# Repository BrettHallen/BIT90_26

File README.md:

# BIT90/26
An attempted recreation of the BIT90 computer released by Bit Corporation (普澤有限公司) in 1983 that is about [US$90,000 (AU$125,000) cheaper than a used one](https://web.archive.org/web/20260206154213/https://www.ebay.com/itm/127471879150):<br>
- Z80 CPU
- TMS9929A VDP
- 2KB RAM (one TC5517/4016 SRAM) expandable to 32KB (expansion cartridge)
- 16KB VRAM (eight 4116 DRAM)
- 24KB ROM (two 2364 + one 2764 or a variation) containing BASIC & Colecovision firmware (?)
- RF & composite video output
- two joystick ports
- Colecovision cartridge/tape compatible (2x15 pin)
- combination audio/video/tape port (DE9)
- expansion edge connector (2x30 pin)
- 5-pin DIN for power (±5V & +12V)

Heavily relying on all the excellent information shared by [b3rendsh](https://github.com/b3rendsh) in their [BIT90 repository](https://github.com/b3rendsh/bit90).<br>

## [Part 1](/KiCad/BIT90_Original/) - Completed (enough)
The initial aim of the project is to recreate the original schematics in KiCad:<br>
- Sheet 6-1 (Processor): ✅ completed
- Sheet 6-2 (Video Control): ✅ completed
- Sheet 6-3 (Joystick, Audio, Tape): ✅ completed
- Sheet 6-4 (Keyboard): ✅ completed
- Sheet 6-5 (PAL Video Encoder): ❌ lost interest, using a Pico9918 so no point
- Sheet 6-6 (Expansion): ✅ completed
- Sheet 7-5 (PAL Video Encoder/32K): ❌ not needed for recreation
- 32K DRAM (4416x4): 🤔 pending, if I can get the base model working

The Video Encoder schematic isn't really relevant to my proposed re-design so haven't bothered completing them.<br>

Sheet 7-5 and the 32KB DRAM sheets appear to be for an updated system with 32KB of RAM?  This would be the ultimate aim, but let's see if we can get the initial 8KB system working.<br>

## Part 2 - Ongoing
The second part will be to try to create a modern replica as a single board computer.<br>

Ideally:
- integrated keyboard
- upgraded 8KB of RAM
- replace VDP9929A & 16KB DRAM with a [Pico9918](https://github.com/visrealm/pico9918)
- HDMI video output (thanks to the Pico9918)
- replace tri-voltage ±5VDC & 12VDC power requirement with a single 5VDC via USB or 2.1mm socket

The main hurdle would be sourcing the SN76489AN sound generator but I don't think this is ... currently (June 2026) ... too difficult. If you are wary of Chinese sellers, a reliable source of genuine parts is [Unicorn Electronics](https://unicornelectronics.com/IC/GENERATORS.html) in the US.  Grab yourself some EPROMs or exotic CPUs whilst you're there.<br>

## Keyboard
Recreation of the original keyboard layout.<br>
Designed with [Keyboard Layout Editor](https://www.keyboard-layout-editor.com/) which generates a JOSN file that can be used to generate a template for the key switches with [Plate & Case Builder](http://builder.swillkb.com).<br>

## ROMs
The original ROMs (BASIC v3.0) have been dumped and can be found [here](https://forums.atariage.com/topic/296435-bit-90-computer-roms-finally-dumped/).<br>

## BBC Basic
You can now also use a version of BBC Basic on the BIT90 thanks to [b3rendsh's](https://github.com/b3rendsh) work developing [BBX80](https://github.com/b3rendsh/bbx80).<br>

## Status
- 3/JUN/2026: Working on [Part 1](/KiCad/BIT90_Original/)
- 4/JUN/2026: Keyboard layout re-created & template generated
- 5/JUN/2026: Initial redesign [(schematic)](/KiCad/BIT90_26/) completed, error checking/fixing to follow
- 6/JUN/2026: PCB layout started

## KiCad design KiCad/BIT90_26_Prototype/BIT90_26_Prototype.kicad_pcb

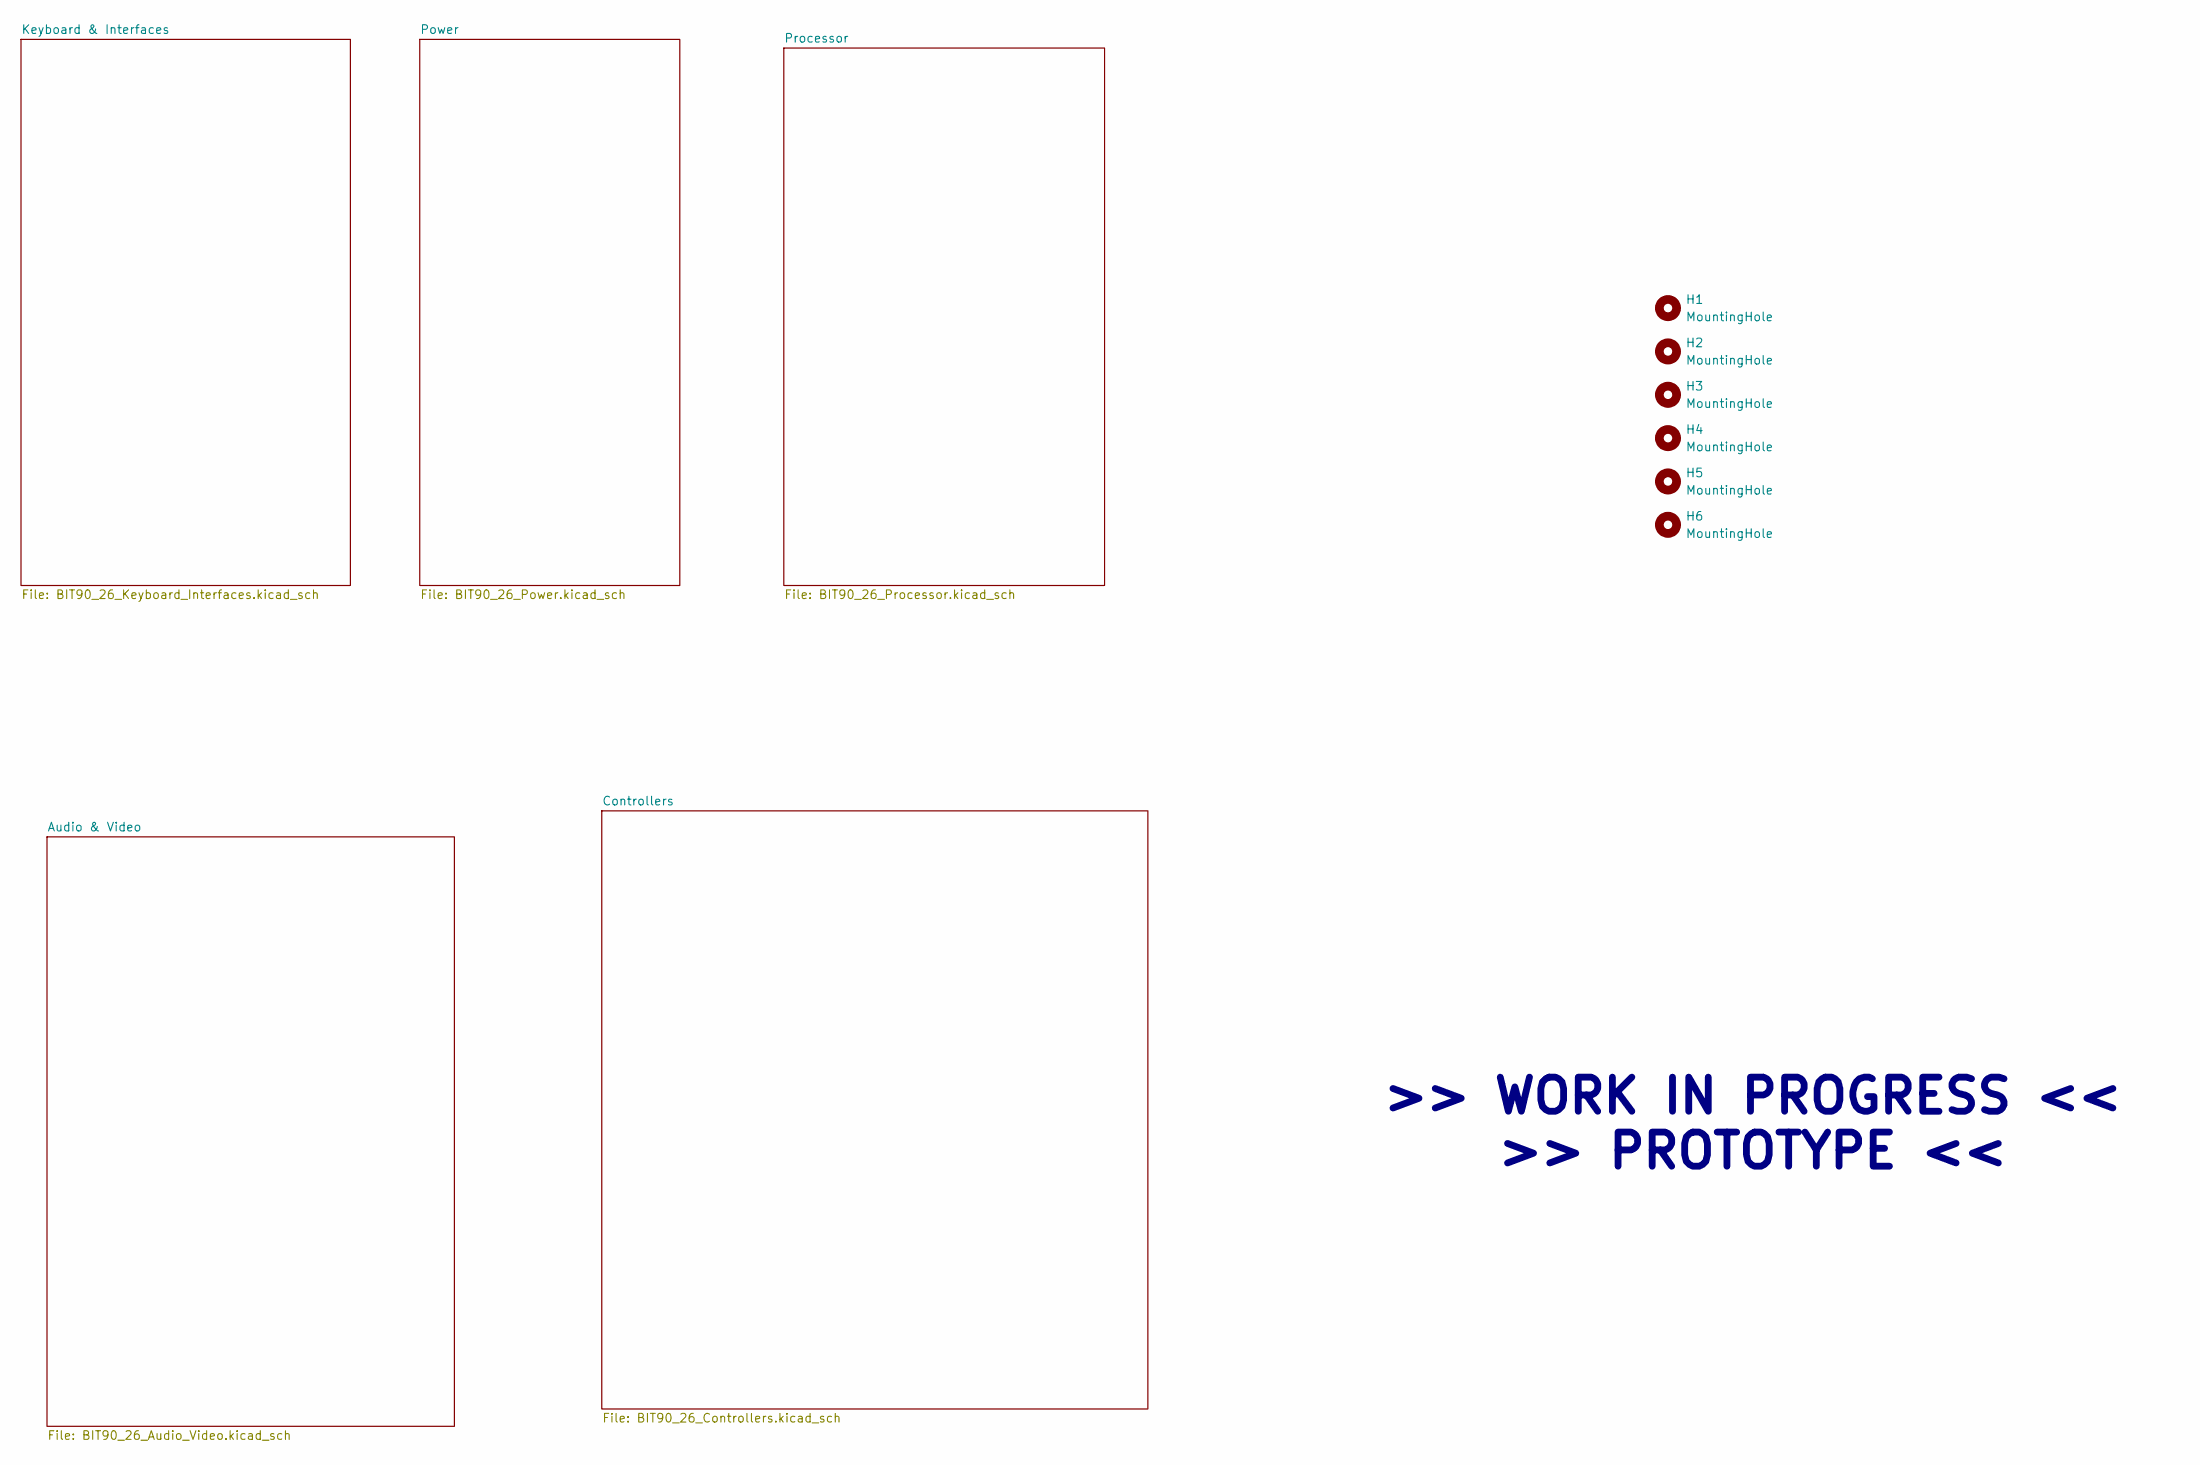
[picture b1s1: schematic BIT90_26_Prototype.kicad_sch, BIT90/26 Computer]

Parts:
H1, H2, H3, H4, H5, H6: MountingHole; MountingHole_3.2mm_M3

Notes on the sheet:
>> WORK IN PROGRESS << >> PROTOTYPE <<

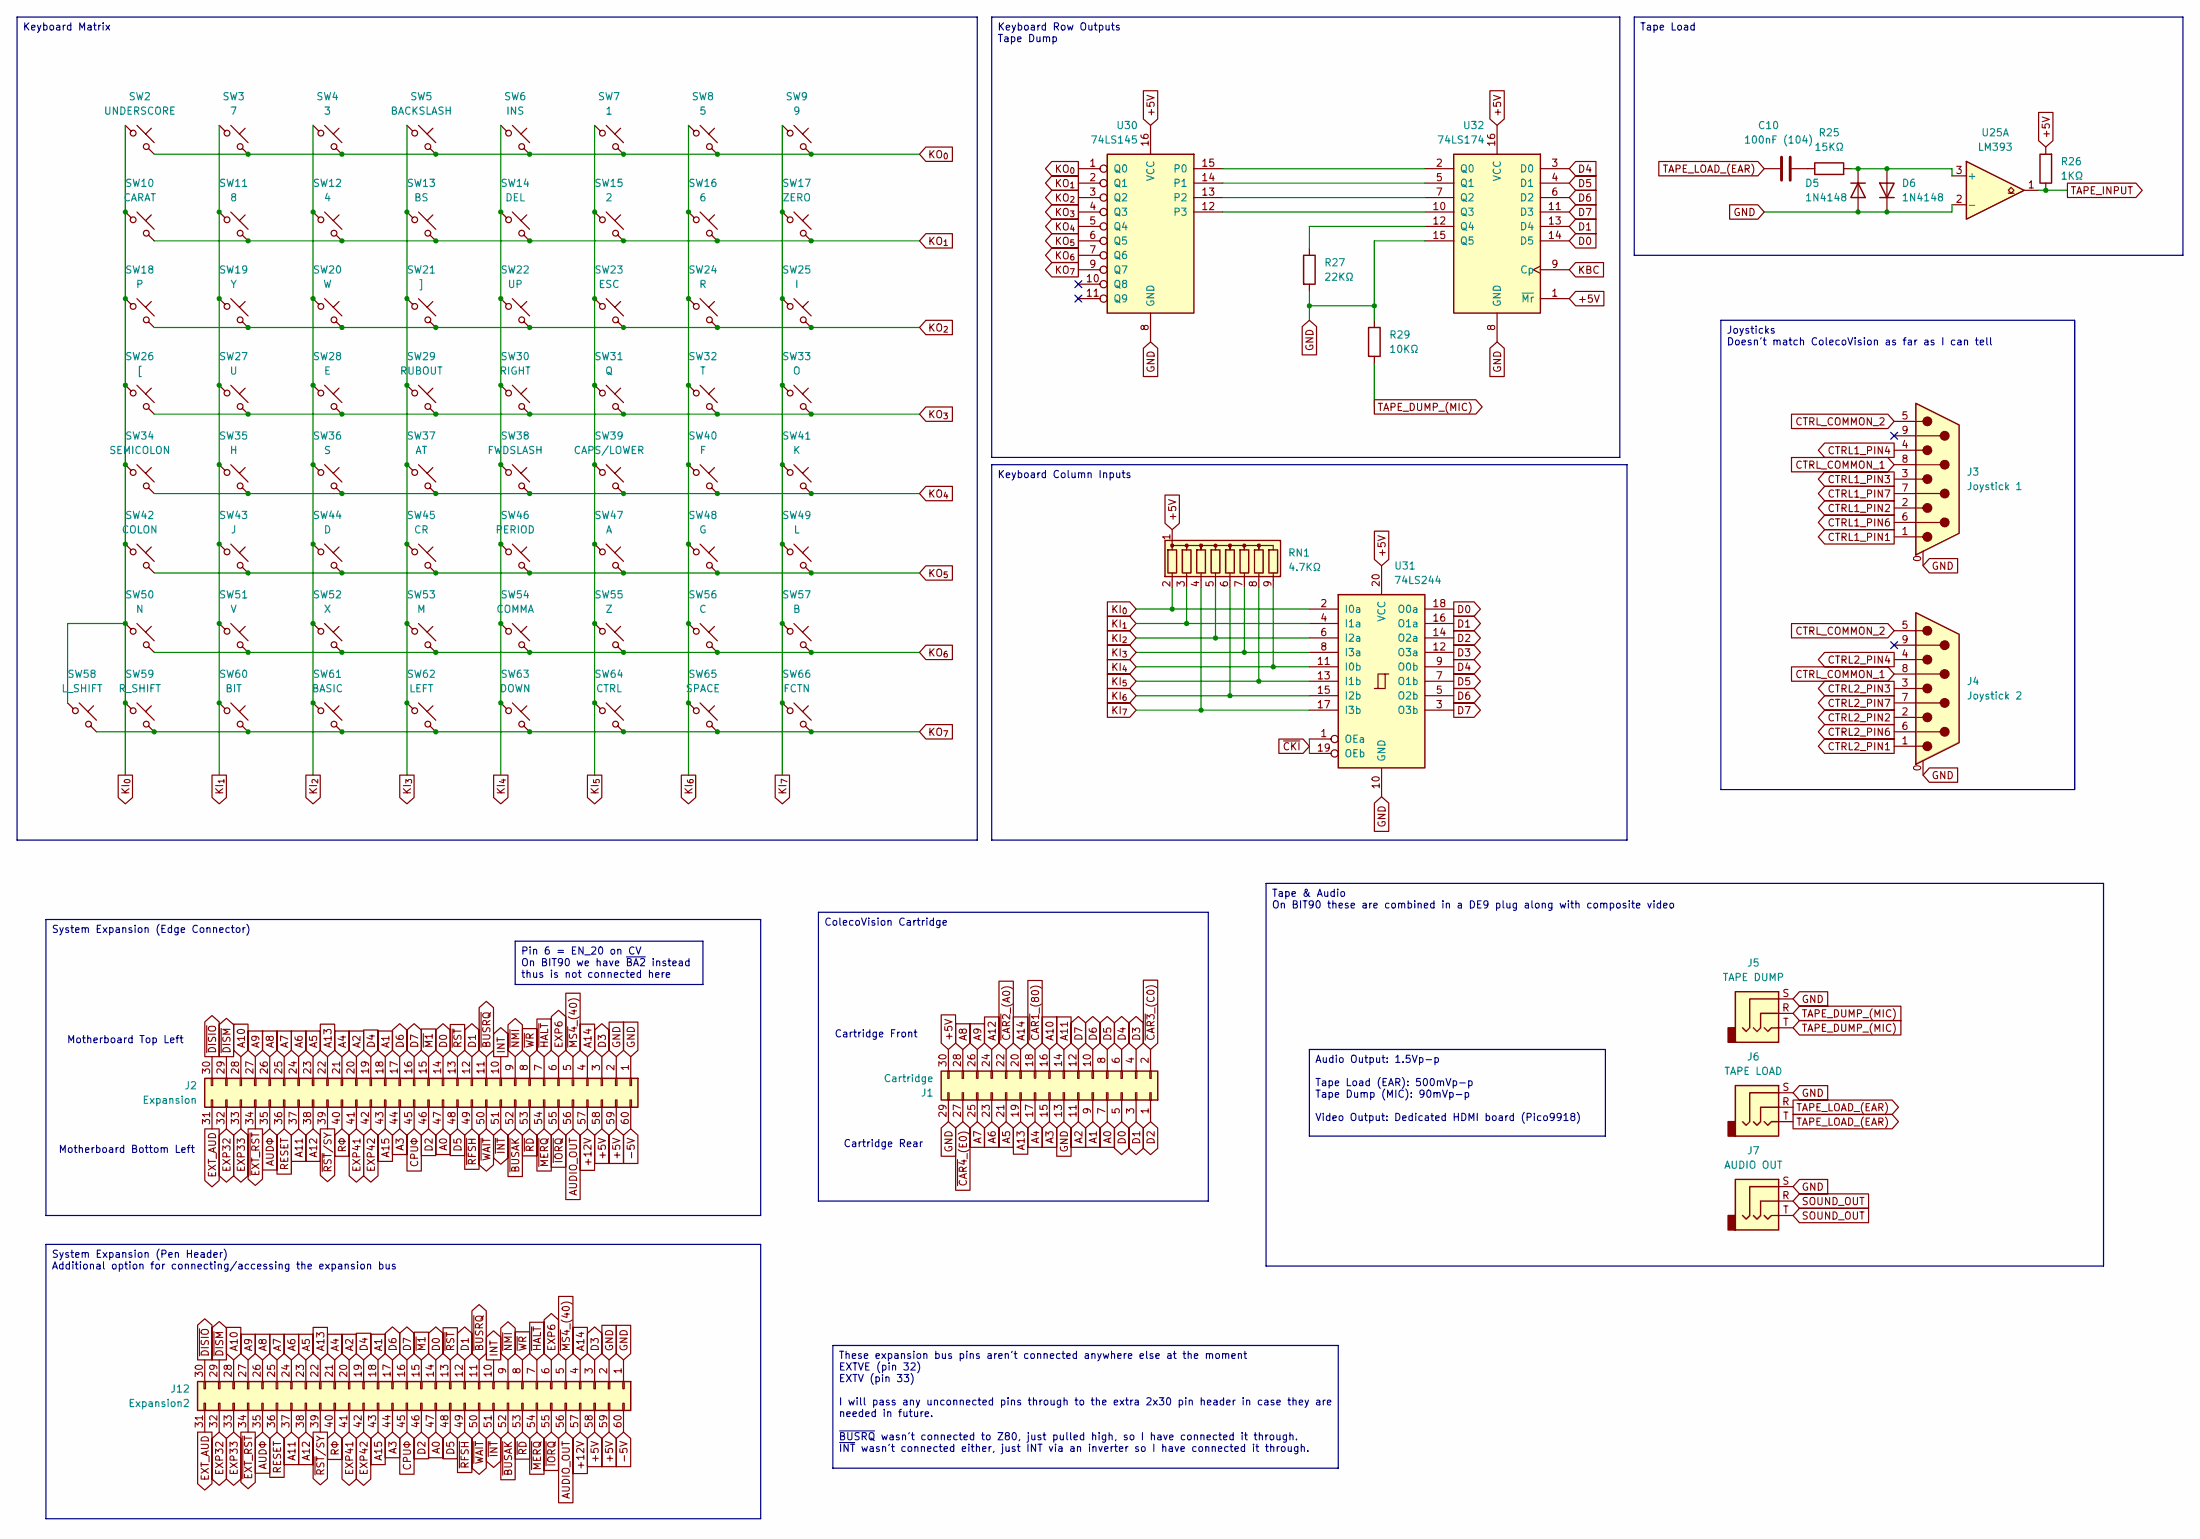
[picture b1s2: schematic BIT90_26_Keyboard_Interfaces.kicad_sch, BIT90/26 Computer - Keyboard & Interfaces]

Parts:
C10: 100nF (104); C_Disc_D3.4mm_W2.1mm_P2.50mm
D5, D6: 1N4148; D_DO-35_SOD27_P7.62mm_Horizontal
J1: Cartridge; CONN30_2x15_DRXN_SUL
J2: Expansion; BIT90 Expansion
J3: Joystick 1; DSUB-9_Pins_Horizontal_P2.77x2.84mm_EdgePinOffset7.70mm_Hou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
J4: Joystick 2; DSUB-9_Pins_Horizontal_P2.77x2.84mm_EdgePinOffset7.70mm_Hou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
J5: TAPE DUMP; SJ335083ATR
J6: TAPE LOAD; SJ335083ATR
J7: AUDIO OUT; SJ335083ATR
J12: Expansion2; PinHeader_2x30_P2.54mm_Vertical
R25: 15KΩ; R_Axial_DIN0207_L6.3mm_D2.5mm_P7.62mm_Horizontal
R26: 1KΩ; R_Axial_DIN0207_L6.3mm_D2.5mm_P7.62mm_Horizontal
R27: 22KΩ; R_Axial_DIN0207_L6.3mm_D2.5mm_P7.62mm_Horizontal
R29: 10KΩ; R_Axial_DIN0207_L6.3mm_D2.5mm_P7.62mm_Horizontal
RN1: 4.7KΩ; R_Array_SIP9
SW2: UNDERSCORE; SW_Gateron_LowProfile_THT
SW3: 7; SW_Gateron_LowProfile_THT
SW4: 3; SW_Gateron_LowProfile_THT
SW5: BACKSLASH; SW_Gateron_LowProfile_THT
SW6: INS; SW_Gateron_LowProfile_THT
SW7: 1; SW_Gateron_LowProfile_THT
SW8: 5; SW_Gateron_LowProfile_THT
SW9: 9; SW_Gateron_LowProfile_THT
SW10: CARAT; SW_Gateron_LowProfile_THT
SW11: 8; SW_Gateron_LowProfile_THT
SW12: 4; SW_Gateron_LowProfile_THT
SW13: BS; SW_Gateron_LowProfile_THT
SW14: DEL; SW_Gateron_LowProfile_THT
SW15: 2; SW_Gateron_LowProfile_THT
SW16: 6; SW_Gateron_LowProfile_THT
SW17: ZERO; SW_Gateron_LowProfile_THT
SW18: P; SW_Gateron_LowProfile_THT
SW19: Y; SW_Gateron_LowProfile_THT
SW20: W; SW_Gateron_LowProfile_THT
SW21: ]; SW_Gateron_LowProfile_THT
SW22: UP; SW_Gateron_LowProfile_THT
SW23: ESC; SW_Gateron_LowProfile_THT
SW24: R; SW_Gateron_LowProfile_THT
SW25: I; SW_Gateron_LowProfile_THT
SW26: [; SW_Gateron_LowProfile_THT
SW27: U; SW_Gateron_LowProfile_THT
SW28: E; SW_Gateron_LowProfile_THT
SW29: RUBOUT; SW_Gateron_LowProfile_THT
SW30: RIGHT; SW_Gateron_LowProfile_THT
SW31: Q; SW_Gateron_LowProfile_THT
SW32: T; SW_Gateron_LowProfile_THT
SW33: O; SW_Gateron_LowProfile_THT
SW34: SEMICOLON; SW_Gateron_LowProfile_THT
SW35: H; SW_Gateron_LowProfile_THT
SW36: S; SW_Gateron_LowProfile_THT
SW37: AT; SW_Gateron_LowProfile_THT
SW38: FWDSLASH; SW_Gateron_LowProfile_THT
SW39: CAPS/LOWER; SW_Gateron_LowProfile_THT
SW40: F; SW_Gateron_LowProfile_THT
SW41: K; SW_Gateron_LowProfile_THT
SW42: COLON; SW_Gateron_LowProfile_THT
SW43: J; SW_Gateron_LowProfile_THT
SW44: D; SW_Gateron_LowProfile_THT
SW45: CR; SW_Gateron_LowProfile_THT
SW46: PERIOD; SW_Gateron_LowProfile_THT
SW47: A; SW_Gateron_LowProfile_THT
SW48: G; SW_Gateron_LowProfile_THT
SW49: L; SW_Gateron_LowProfile_THT
SW50: N; SW_Gateron_LowProfile_THT
SW51: V; SW_Gateron_LowProfile_THT
SW52: X; SW_Gateron_LowProfile_THT
SW53: M; SW_Gateron_LowProfile_THT
SW54: COMMA; SW_Gateron_LowProfile_THT
SW55: Z; SW_Gateron_LowProfile_THT
SW56: C; SW_Gateron_LowProfile_THT
SW57: B; SW_Gateron_LowProfile_THT
SW58: L_SHIFT; SW_Gateron_LowProfile_THT
SW59: R_SHIFT; SW_Gateron_LowProfile_THT
SW60: BIT; SW_Gateron_LowProfile_THT
SW61: BASIC; SW_Gateron_LowProfile_THT
SW62: LEFT; SW_Gateron_LowProfile_THT
SW63: DOWN; SW_Gateron_LowProfile_THT
SW64: CTRL; SW_Gateron_LowProfile_THT
SW65: SPACE; SW_Gateron_LowProfile_THT
SW66: FCTN; SW_Gateron_LowProfile_THT
U25: LM393; DIP-8_W7.62mm
U30: 74LS145; DIP-16_W7.62mm
U31: 74LS244; DIP-20_W7.62mm
U32: 74LS174; DIP-16_W7.62mm

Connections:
+5V: J1.30, J2.58, J2.59, J12.58, J12.59, R26.2, RN1.1 (common), U30.16 (VCC), U31.20 (VCC), U32.1 (~Mr), U32.16 (VCC); also elsewhere on the board
+12V: J2.57, J12.57; also elsewhere on the board
-5V: J2.60, J12.60; also elsewhere on the board
A0: J1.7, J2.47, J12.47; also elsewhere on the board
A1: J1.9, J2.18, J12.18; also elsewhere on the board
A2: J1.11, J2.20, J12.20; also elsewhere on the board
A3: J1.15, J2.44, J12.44; also elsewhere on the board
A4: J1.17, J2.21, J12.21; also elsewhere on the board
A5: J1.21, J2.23, J12.23; also elsewhere on the board
A6: J1.23, J2.24, J12.24; also elsewhere on the board
A7: J1.25, J2.25, J12.25; also elsewhere on the board
A8: J1.28, J2.26, J12.26; also elsewhere on the board
A9: J1.26, J2.27, J12.27; also elsewhere on the board
A10: J1.16, J2.28, J12.28; also elsewhere on the board
A11: J1.14, J2.37, J12.37; also elsewhere on the board
A12: J1.24, J2.38, J12.38; also elsewhere on the board
A13: J1.19, J2.22, J12.22; also elsewhere on the board
A14: J1.20, J2.4, J12.4; also elsewhere on the board
A15: J2.43, J12.43; also elsewhere on the board
AUDIO_OUT: J2.56, J12.56; also elsewhere on the board
AUDΦ: J2.35, J12.35; also elsewhere on the board
CPUΦ: J2.45, J12.45; also elsewhere on the board
CTRL1_PIN1: J3.1; also elsewhere on the board
CTRL1_PIN2: J3.2; also elsewhere on the board
CTRL1_PIN3: J3.3; also elsewhere on the board
CTRL1_PIN4: J3.4; also elsewhere on the board
CTRL1_PIN6: J3.6; also elsewhere on the board
CTRL1_PIN7: J3.7; also elsewhere on the board
CTRL2_PIN1: J4.1; also elsewhere on the board
CTRL2_PIN2: J4.2; also elsewhere on the board
CTRL2_PIN3: J4.3; also elsewhere on the board
CTRL2_PIN4: J4.4; also elsewhere on the board
CTRL2_PIN6: J4.6; also elsewhere on the board
CTRL2_PIN7: J4.7; also elsewhere on the board
CTRL_COMMON_1: J3.8, J4.8; also elsewhere on the board
CTRL_COMMON_2: J3.5, J4.5; also elsewhere on the board
D0: J1.5, J2.14, J12.14, U31.18 (O0a), U32.14 (D5); also elsewhere on the board
D1: J1.3, J2.12, J12.12, U31.16 (O1a), U32.13 (D4); also elsewhere on the board
D2: J1.1, J2.46, J12.46, U31.14 (O2a); also elsewhere on the board
D3: J1.4, J2.3, J12.3, U31.12 (O3a); also elsewhere on the board
D4: J1.6, J2.19, J12.19, U31.9 (O0b), U32.3 (D0); also elsewhere on the board
D5: J1.8, J2.48, J12.48, U31.7 (O1b), U32.4 (D1); also elsewhere on the board
D6: J1.10, J2.17, J12.17, U31.5 (O2b), U32.6 (D2); also elsewhere on the board
D7: J1.12, J2.16, J12.16, U31.3 (O3b), U32.11 (D3); also elsewhere on the board
EXP6: J2.6, J12.6
EXP32: J2.32, J12.32
EXP33: J2.33, J12.33
EXP41: J2.41, J12.41
EXP42: J2.42, J12.42
EXT_AUD: J2.31, J12.31; also elsewhere on the board
GND: D5.2 (A), D6.1 (K), J1.13, J1.29, J2.1, J2.2, J3.0 (SH), J4.0 (SH), J5.S, J6.S, J7.S, J12.1, J12.2, R27.2, R29.1, U25.2 (-), U30.8 (GND), U31.10 (GND), U32.8 (GND), U32.15 (Q5); also elsewhere on the board
INT: J2.10, J12.10; also elsewhere on the board
KBC: U32.9 (Cp); also elsewhere on the board
KI_{0}: RN1.2 (R1), SW2.1, SW10.1, SW18.1, SW26.1, SW34.1, SW42.1, SW50.1, SW58.1, SW59.1, U31.2 (I0a)
KI_{1}: RN1.3 (R2), SW3.1, SW11.1, SW19.1, SW27.1, SW35.1, SW43.1, SW51.1, SW60.1, U31.4 (I1a)
KI_{2}: RN1.5 (R4), SW4.1, SW12.1, SW20.1, SW28.1, SW36.1, SW44.1, SW52.1, SW61.1, U31.6 (I2a)
KI_{3}: RN1.7 (R6), SW5.1, SW13.1, SW21.1, SW29.1, SW37.1, SW45.1, SW53.1, SW62.1, U31.8 (I3a)
KI_{4}: RN1.9 (R8), SW6.1, SW14.1, SW22.1, SW30.1, SW38.1, SW46.1, SW54.1, SW63.1, U31.11 (I0b)
KI_{5}: RN1.8 (R7), SW7.1, SW15.1, SW23.1, SW31.1, SW39.1, SW47.1, SW55.1, SW64.1, U31.13 (I1b)
KI_{6}: RN1.6 (R5), SW8.1, SW16.1, SW24.1, SW32.1, SW40.1, SW48.1, SW56.1, SW65.1, U31.15 (I2b)
KI_{7}: RN1.4 (R3), SW9.1, SW17.1, SW25.1, SW33.1, SW41.1, SW49.1, SW57.1, SW66.1, U31.17 (I3b)
KO_{0}: SW2.2, SW3.2, SW4.2, SW5.2, SW6.2, SW7.2, SW8.2, SW9.2, U30.1 (Q0)
KO_{1}: SW10.2, SW11.2, SW12.2, SW13.2, SW14.2, SW15.2, SW16.2, SW17.2, U30.2 (Q1)
KO_{2}: SW18.2, SW19.2, SW20.2, SW21.2, SW22.2, SW23.2, SW24.2, SW25.2, U30.3 (Q2)
KO_{3}: SW26.2, SW27.2, SW28.2, SW29.2, SW30.2, SW31.2, SW32.2, SW33.2, U30.4 (Q3)
KO_{4}: SW34.2, SW35.2, SW36.2, SW37.2, SW38.2, SW39.2, SW40.2, SW41.2, U30.5 (Q4)
KO_{5}: SW42.2, SW43.2, SW44.2, SW45.2, SW46.2, SW47.2, SW48.2, SW49.2, U30.6 (Q5)
KO_{6}: SW50.2, SW51.2, SW52.2, SW53.2, SW54.2, SW55.2, SW56.2, SW57.2, U30.7 (Q6)
KO_{7}: SW58.2, SW59.2, SW60.2, SW61.2, SW62.2, SW63.2, SW64.2, SW65.2, SW66.2, U30.9 (Q7)
unnamed: C10.2, R25.1
unnamed: D5.1 (K), D6.2 (A), R25.2, U25.3 (+)
unnamed: U30.15 (P0), U32.2 (Q0)
unnamed: U30.14 (P1), U32.5 (Q1)
unnamed: U30.13 (P2), U32.7 (Q2)
unnamed: U30.12 (P3), U32.10 (Q3)
unnamed: R27.1, U32.12 (Q4)
RESET: J2.36, J12.36; also elsewhere on the board
RΦ: J2.40, J12.40; also elsewhere on the board
SOUND_OUT: J7.R, J7.T; also elsewhere on the board
TAPE_DUMP_(MIC): J5.R, J5.T, R29.2
TAPE_INPUT: R26.1, U25.1; also elsewhere on the board
TAPE_LOAD_(EAR): C10.1, J6.R, J6.T
~BUSAK: J2.52, J12.52; also elsewhere on the board
~BUSRQ: J2.11, J12.11; also elsewhere on the board
~CAR1_(80): J1.18; also elsewhere on the board
~CAR2_(A0): J1.22; also elsewhere on the board
~CAR3_(C0): J1.2; also elsewhere on the board
~CAR4_(E0): J1.27; also elsewhere on the board
~CKI: U31.1 (OEa), U31.19 (OEb); also elsewhere on the board
~DISIO: J2.30, J12.30; also elsewhere on the board
~DISM: J2.29, J12.29; also elsewhere on the board
~EXT_RST: J2.34, J12.34; also elsewhere on the board
~HALT: J2.7, J12.7; also elsewhere on the board
~INT: J2.51, J12.51; also elsewhere on the board
~IORQ: J2.55, J12.55; also elsewhere on the board
~M1: J2.15, J12.15; also elsewhere on the board
~MERQ: J2.54, J12.54; also elsewhere on the board
~MS4_(40): J2.5, J12.5; also elsewhere on the board
~NMI: J2.9, J12.9; also elsewhere on the board
~RD: J2.53, J12.53; also elsewhere on the board
~RFSH: J2.49, J12.49; also elsewhere on the board
~RST: J2.13, J12.13; also elsewhere on the board
~RST/SY: J2.39, J12.39; also elsewhere on the board
~WAIT: J2.50, J12.50; also elsewhere on the board
~WR: J2.8, J12.8; also elsewhere on the board

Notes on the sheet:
Motherboard Top Left
Motherboard Bottom Left
Cartridge Rear
Cartridge Front
Joysticks Doesn't match ColecoVision as far as I can tell
Keyboard Row Outputs Tape Dump
ColecoVision Cartridge
Tape Load
Pin 6 = EN_20 on CV On BIT90 we have ~{BA2} instead thus is not connected here
System Expansion (Edge Connector)
System Expansion (Pen Header) Additional option for connecting/accessing the expansion bus
Audio Output: 1.5Vp-p Tape Load (EAR): 500mVp-p Tape Dump (MIC): 90mVp-p Video Output: Dedicated HDMI board (Pico9918)
Tape & Audio On BIT90 these are combined in a DE9 plug along with composite video
Keyboard Column Inputs
These expansion bus pins aren't connected anywhere else at the moment EXTVE (pin 32) EXTV (pin 33) I will pass any unconnected pins through to the extra 2x30 pin header in case they are needed in future. ~{BUSRQ} wasn't connected to Z80, just pulled high, so I have connected it through. ~{INT} wasn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
Keyboard Matrix

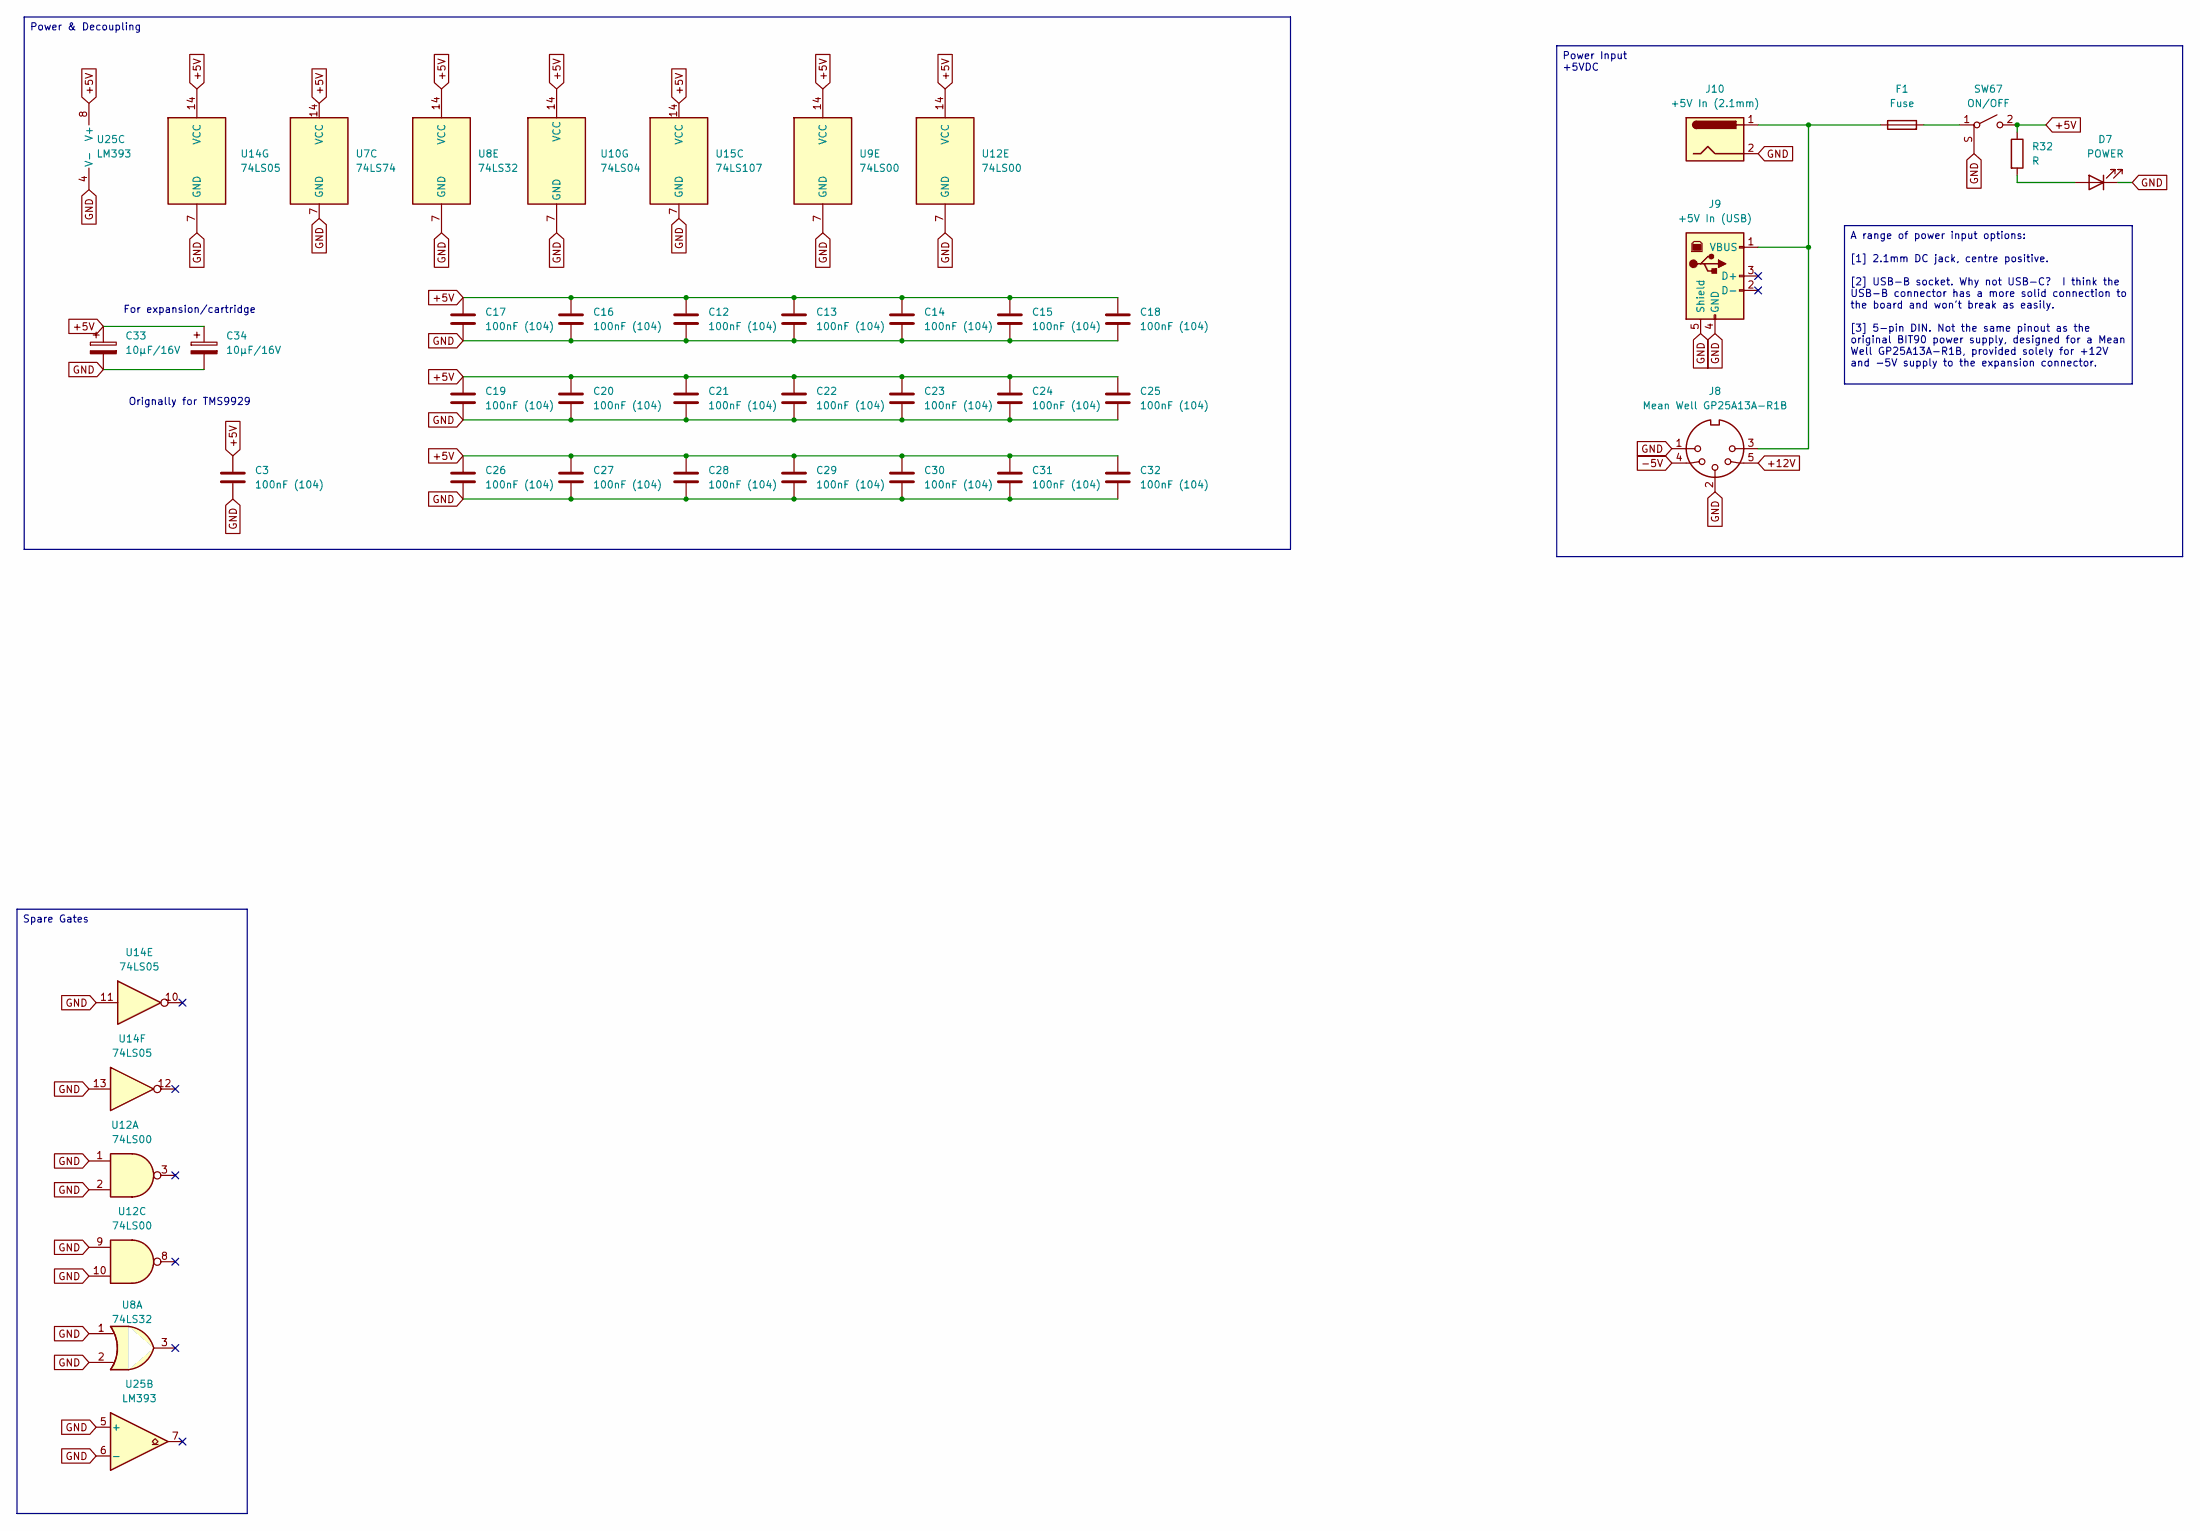
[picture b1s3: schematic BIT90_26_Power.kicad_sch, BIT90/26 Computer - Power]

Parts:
C3, C12, C13, C14, C15, C16, C17, C18, C19, C20, C21, C22, C23, C24, C25, C26, C27, C28, C29, C30, C31, C32: 100nF (104); C_Disc_D3.4mm_W2.1mm_P2.50mm
C33, C34: 10µF/16V; CP_Radial_D6.3mm_P2.50mm
D7: POWER; LED_D5.0mm
F1: Fuse; Fuseholder_Clip-5x20mm_Littelfuse_111_Inline_P20.00x5.00mm_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
J8: Mean Well GP25A13A-R1B; SDF80J
J9: +5V In (USB); USB_B_Lumberg_2411_02_Horizontal
J10: +5V In (2.1mm); BarrelJack_Horizontal
R32: R; R_Axial_DIN0207_L6.3mm_D2.5mm_P7.62mm_Horizontal
SW67: ON/OFF; SW_400MSP1R6BLKM6QE
U7: 74LS74; DIP-14_W7.62mm
U8: 74LS32; DIP-14_W7.62mm
U9, U12: 74LS00; DIP-14_W7.62mm
U10: 74LS04; DIP-14_W7.62mm
U14: 74LS05; DIP-14_W7.62mm
U15: 74LS107; DIP-14_W7.62mm
U25: LM393; DIP-8_W7.62mm

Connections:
+5V: C3.1, C12.1, C13.1, C14.1, C15.1, C16.1, C17.1, C18.1, C19.1, C20.1, C21.1, C22.1, C23.1, C24.1, C25.1, C26.1, C27.1, C28.1, C29.1, C30.1, C31.1, C32.1, C33.1, C34.1, R32.1, SW67.2 (B), U7.14 (VCC), U8.14 (VCC), U9.14 (VCC), U10.14 (VCC), U12.14 (VCC), U14.14 (VCC), U15.14 (VCC), U25.8 (V+); also elsewhere on the board
+12V: J8.5; also elsewhere on the board
-5V: J8.4; also elsewhere on the board
GND: C3.2, C12.2, C13.2, C14.2, C15.2, C16.2, C17.2, C18.2, C19.2, C20.2, C21.2, C22.2, C23.2, C24.2, C25.2, C26.2, C27.2, C28.2, C29.2, C30.2, C31.2, C32.2, C33.2, C34.2, D7.1 (K), J8.1, J8.2, J9.4 (GND), J9.5 (Shield), J10.2, SW67.S (SPT), U7.7 (GND), U8.1, U8.2, U8.7 (GND), U9.7 (GND), U10.7 (GND), U12.1, U12.2, U12.7 (GND), U12.9, U12.10, U14.7 (GND), U14.11, U14.13, U15.7 (GND), U25.4 (V-), U25.5 (+), U25.6 (-); also elsewhere on the board
unnamed: D7.2 (A), R32.2
unnamed: F1.1, J8.3, J9.1 (VBUS), J10.1
unnamed: F1.2, SW67.1 (A)

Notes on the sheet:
Orignally for TMS9929
For expansion/cartridge
Spare Gates
A range of power input options: [1] 2.1mm DC jack, centre positive. [2] USB-B socket. Why not USB-C? I think the USB-B connector has a more solid connection to the board and won't break as easily. [3] 5-pin DIN. Not the same pinout as the original BIT90 power supply, designed for a Mean Well GP25A1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
Power & Decoupling
Power Input +5VDC

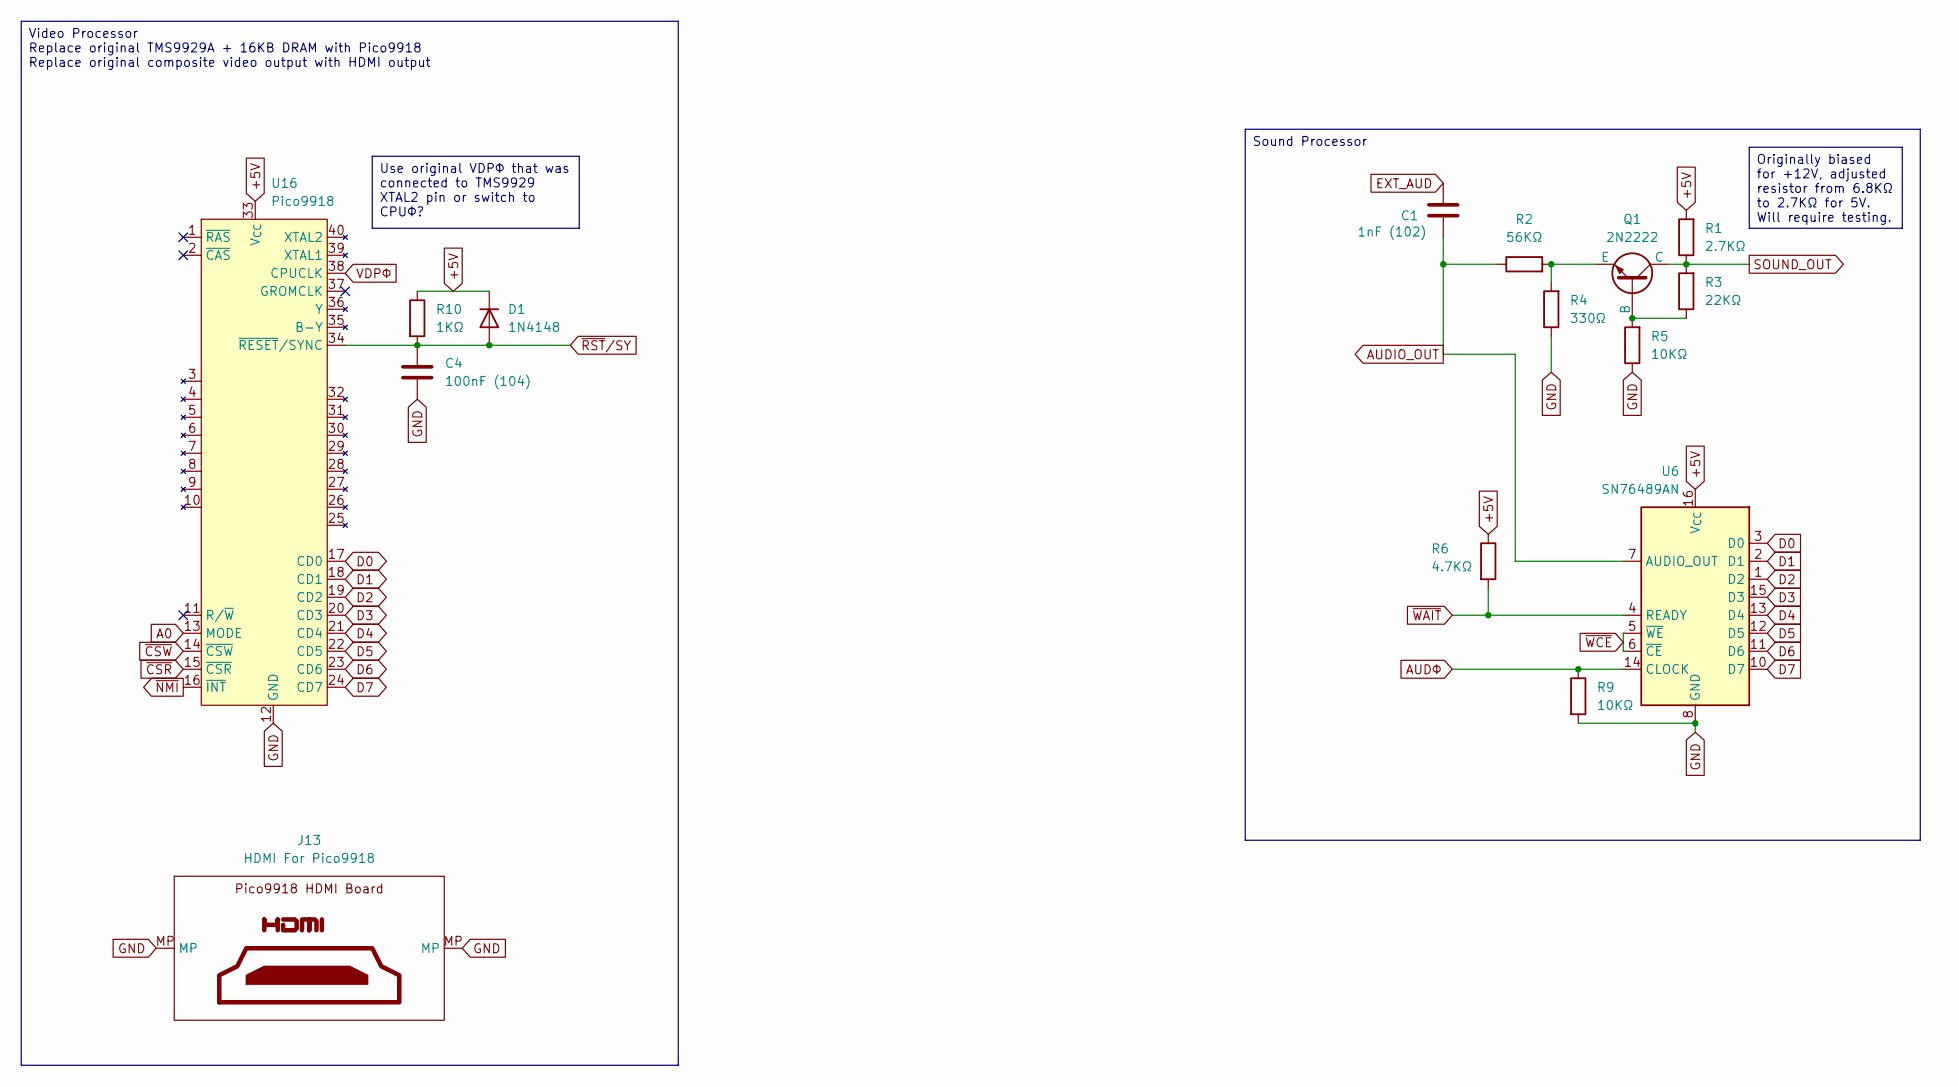
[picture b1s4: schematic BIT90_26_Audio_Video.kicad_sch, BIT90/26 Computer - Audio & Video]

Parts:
C1: 1nF (102); C_Disc_D3.4mm_W2.1mm_P2.50mm
C4: 100nF (104); C_Disc_D3.4mm_W2.1mm_P2.50mm
D1: 1N4148; D_DO-35_SOD27_P7.62mm_Horizontal
J13: HDMI For Pico9918; Pico9918_HDMI_Board
Q1: 2N2222; TO-92_Inline_Wide
R1: 2.7KΩ; R_Axial_DIN0207_L6.3mm_D2.5mm_P7.62mm_Horizontal
R2: 56KΩ; R_Axial_DIN0207_L6.3mm_D2.5mm_P7.62mm_Horizontal
R3: 22KΩ; R_Axial_DIN0207_L6.3mm_D2.5mm_P7.62mm_Horizontal
R4: 330Ω; R_Axial_DIN0207_L6.3mm_D2.5mm_P7.62mm_Horizontal
R5, R9: 10KΩ; R_Axial_DIN0207_L6.3mm_D2.5mm_P7.62mm_Horizontal
R6: 4.7KΩ; R_Axial_DIN0207_L6.3mm_D2.5mm_P7.62mm_Horizontal
R10: 1KΩ; R_Axial_DIN0207_L6.3mm_D2.5mm_P7.62mm_Horizontal
U6: SN76489AN; DIP-16_W7.62mm
U16: Pico9918; DIP-40_W15.24mm_Socket

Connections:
+5V: D1.1 (K), R1.2, R6.1, R10.1, U6.16 (V_{CC}), U16.33 (V_{CC}); also elsewhere on the board
A0: U16.13 (MODE); also elsewhere on the board
AUDIO_OUT: C1.2, R2.1, U6.7 (AUDIO_OUT); also elsewhere on the board
AUDΦ: R9.1, U6.14 (CLOCK); also elsewhere on the board
D0: U6.3 (D0), U16.17 (CD0); also elsewhere on the board
D1: U6.2 (D1), U16.18 (CD1); also elsewhere on the board
D2: U6.1 (D2), U16.19 (CD2); also elsewhere on the board
D3: U6.15 (D3), U16.20 (CD3); also elsewhere on the board
D4: U6.13 (D4), U16.21 (CD4); also elsewhere on the board
D5: U6.12 (D5), U16.22 (CD5); also elsewhere on the board
D6: U6.11 (D6), U16.23 (CD6); also elsewhere on the board
D7: U6.10 (D7), U16.24 (CD7); also elsewhere on the board
EXT_AUD: C1.1; also elsewhere on the board
GND: C4.2, J13.MP, R4.1, R5.1, R9.2, U6.8 (GND), U16.12 (GND); also elsewhere on the board
unnamed: Q1.2 (B), R3.1, R5.2
unnamed: Q1.3 (E), R2.2, R4.2
SOUND_OUT: Q1.1 (C), R1.1, R3.2; also elsewhere on the board
VDPΦ: U16.38 (CPUCLK); also elsewhere on the board
~CSR: U16.15 (~CSR); also elsewhere on the board
~CSW: U16.14 (~CSW); also elsewhere on the board
~NMI: U16.16 (~INT); also elsewhere on the board
~RST/SY: C4.1, D1.2 (A), R10.2, U16.34 (~RESET/SYNC); also elsewhere on the board
~WAIT: R6.2, U6.4 (READY); also elsewhere on the board
~WCE: U6.5 (~WE), U6.6 (~CE); also elsewhere on the board

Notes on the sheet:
Video Processor Replace original TMS9929A + 16KB DRAM with Pico9918 Replace original composite video output with HDMI output
Originally biased for +12V, adjusted resistor from 6.8KΩ to 2.7KΩ for 5V. Will require testing.
Sound Processor
Use original VDPΦ that was connected to TMS9929 XTAL2 pin or switch to CPUΦ?
